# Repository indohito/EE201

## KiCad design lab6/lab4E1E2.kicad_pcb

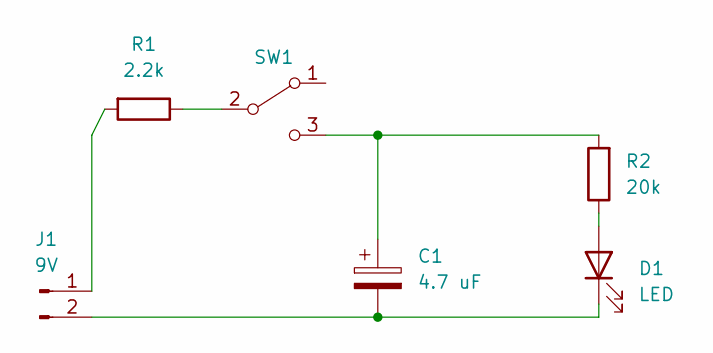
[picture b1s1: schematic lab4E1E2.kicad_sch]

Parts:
C1: 4.7 uF
D1: LED
J1: 9V
R1: 2.2k
R2: 20k
SW1: SW_SPDT

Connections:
unnamed: C1.1, R2.2, SW1.3 (C)
unnamed: C1.2, D1.1 (K), J1.2
unnamed: D1.2 (A), R2.1
unnamed: J1.1, R1.2
unnamed: R1.1, SW1.2 (B)

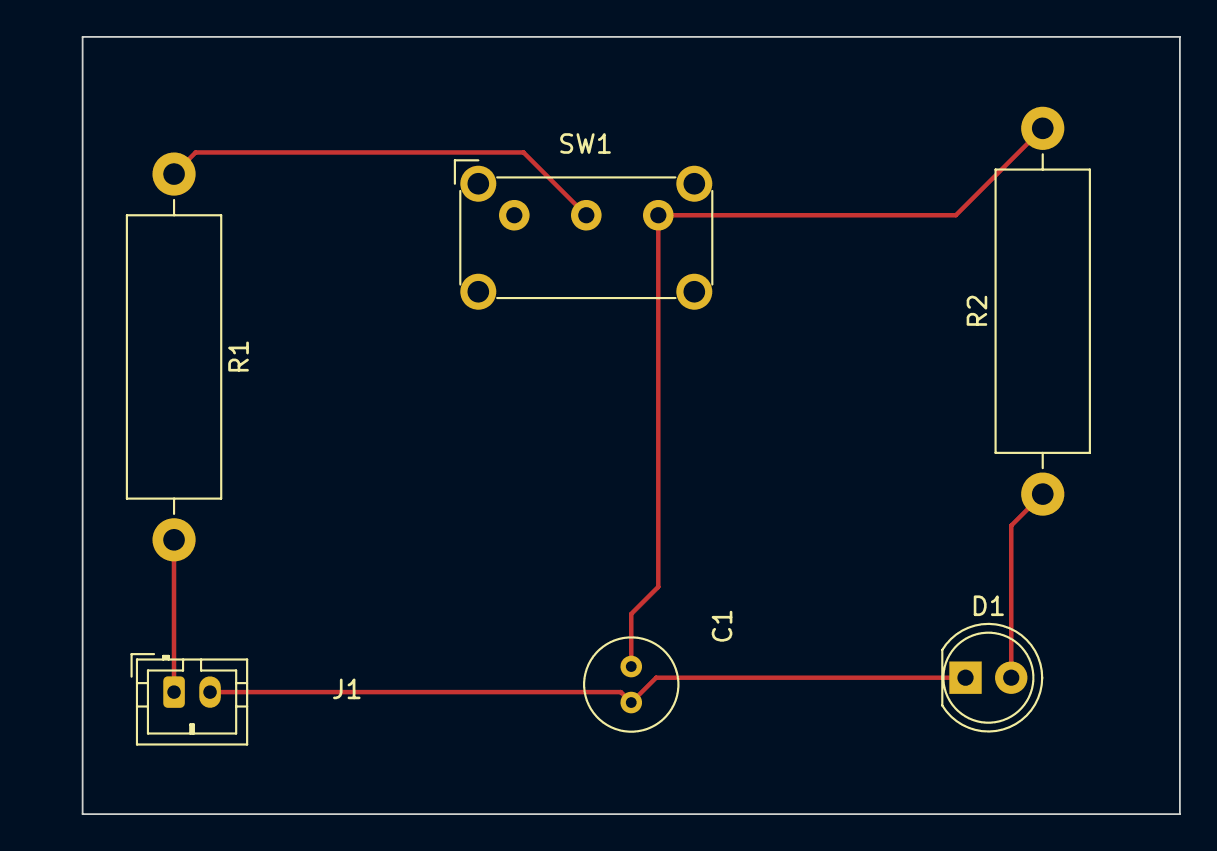
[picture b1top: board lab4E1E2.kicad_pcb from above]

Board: 2 copper layers, 63.5 x 43.2 mm, 6 parts (0 on the bottom side), 5 nets.

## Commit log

2023-01-13 Iniital Commit
2023-01-13 aboutMe commit
2023-01-13 second commit
2023-01-13 edited README
2023-01-13 second README
2023-01-20 arduino
2023-01-31 lab4
2023-02-17 lab6
2023-02-24 lab7
2023-03-13 lab52
2023-03-13 lab8
